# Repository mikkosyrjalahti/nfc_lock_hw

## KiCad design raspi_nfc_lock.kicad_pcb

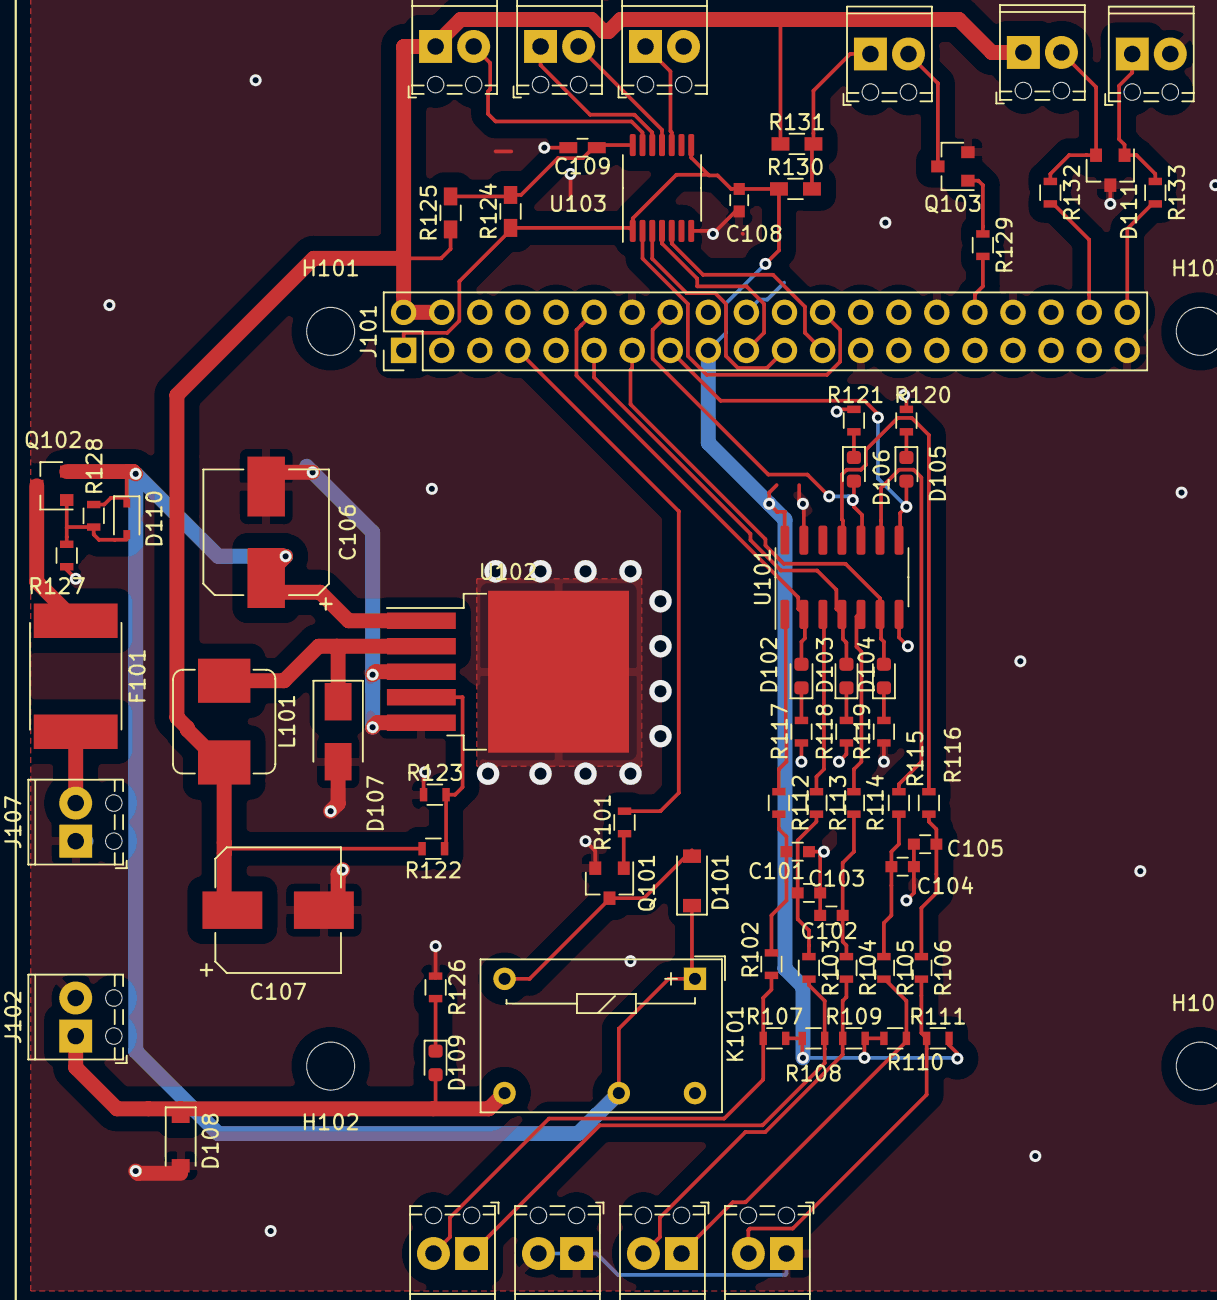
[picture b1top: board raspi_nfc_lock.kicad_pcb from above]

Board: 2 copper layers, 79 parts (0 on the bottom side), 56 nets.

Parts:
C101, C102, C103, C104, C105, C108: 100n; C_0603
C106: 220 μF 25V; CP_Elec_8x10
C107: 680μF 10V; CP_Elec_8x10.5
C109: 100n; C_0603_HandSoldering
D101, D108: SMF15A; D_SOD-123
D102, D103, D104, D105, D106: LED; D_0603_1608Metric
D107: SS34; D_SMA
D109: LED_OPEN; D_0603_1608Metric
D110: MM3Z12; D_SOD-323
D111: SP0502BAHT; SOT-23
F101: Polyfuse 1A; Fuse_SMD2920
H101, H102, H103, H104: MountingHole; MountingHole_3.2mm_M3
J101: Raspberry_Pi_2_3; Pin_Header_Straight_2x20_Pitch2.54mm
J102, J103, J104, J105, J106, J107, J108, J109, J110, J111, J112: Screw_Terminal_01x02; TerminalBlock_Phoenix_MPT-0,5-2-2.54_1x02_P2.54mm_Horizontal
J113: BUZZER; TerminalBlock_Phoenix_MPT-0,5-2-2.54_1x02_P2.54mm_Horizontal
K101: G6E; Relay_SPDT_Omron_G6E
L101: MWSA0603S-330MT; L_Bourns_SRP7028A_7.3x6.6mm
Q101, Q103: MMBT3904; SOT-23
Q102: Si2319CDS; SOT-23
R101, R129: 2k21; R_0603
R102, R103, R104, R105, R106: 10; R_0603
R107, R108, R109, R110, R111, R112, R113, R114, R115, R116, R117, R118, R119, R120, R121, R127: 4k7; R_0603
R122: 3k75; R_0603
R123: 1k21; R_0603
R124, R131: DNI; R_0603_HandSoldering
R125, R130: 0R; R_0603_HandSoldering
R126: 10k; R_0603
R128: 1M; R_0603
R132, R133: 470R; R_0603
U101: 74HC14; SOIC-14_3.9x8.7mm_P1.27mm
U102: LM2596S; TO-263-5_TabPin3
U103: TXB0104PW; TSSOP-14_4.4x5mm_P0.65mm

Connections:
+3V3: C108.1, J101.1, J101.17, R107.2, R108.2, R109.2, R110.2, R111.2, R124.1, R130.1, U101.14, U103.1, U103.8
+5V: C107.1, J101.2, J101.4, J108.1, J110.1, L101.2, R122.2, R125.1, R131.1
+12V: C106.1, D101.1, D110.1, K101.1, K101.10, Q102.2, R128.2, U102.1
/*CE0: J101.24, U103.2
/APA102_CLK: J101.40, R133.2
/APA102_DATA: J101.38, R132.2
/B1: D105.2, J101.15, U101.8
/B2: D106.2, J101.16, U101.10
/BUTTON_1: J105.1, R105.2, R110.1
/BUTTON_2: J106.2, R106.2, R111.1
/BUZZ: J113.2, Q103.3
/BUZZER: J101.32, R129.2
/DOOR: D102.2, J101.12, U101.2
/DOOR_SW: J103.2, R102.2, R107.1
/HANDLE: D104.2, J101.13, U101.6
/HANDLE_SW: J105.2, R104.2, R109.1
/LATCH: D103.2, J101.11, U101.4
/LATCH_SW: J103.1, R103.2, R108.1
/LED_CLK: D111.1, J109.1, R133.1
/LED_DATA: D111.2, J108.2, R132.1
/LOCK_SOLENOID: D108.1, D109.2, J102.1, K101.7
/MISO: J101.21, U103.3
/MOSI: J101.19, U103.4
/NFC_CS: J110.2, U103.13
/NFC_MISO: J111.1, U103.12
/NFC_MOSI: J111.2, U103.11
/NFC_SCK: J112.1, U103.10
/PWR_IN: F101.2, J107.2
/RELAY: J101.7, R101.2
/SCK: J101.23, U103.5
GND: C101.1, C102.1, C103.1, C104.1, C105.1, C106.2, C107.2, C108.2, C109.2, D107.2, D108.2, D111.3, J101.6, J101.9, J101.14, J101.20, J101.25, J101.30, J101.34, J101.39, J102.2, J104.1, J104.2, J106.1, J107.1, J109.2, J112.2, Q101.2, Q103.2, R117.1, R118.1, R119.1, R120.1, R121.1, R123.1, R126.1, R127.1, U101.7, U101.13, U102.3, U102.5, U103.7
unnamed: C101.2, R102.1, R112.2
unnamed: C102.2, R103.1, R113.2
unnamed: C103.2, R104.1, R114.2
unnamed: C104.2, R105.1, R115.2
unnamed: C105.2, R106.1, R116.2
unnamed: C109.1, R124.2, R125.2, U103.14
unnamed: D101.2, K101.6, Q101.3
unnamed: D102.1, R117.2
unnamed: D103.1, R118.2
unnamed: D104.1, R119.2
unnamed: D105.1, R120.2
unnamed: D106.1, R121.2
unnamed: D107.1, L101.1, U102.2
unnamed: D109.1, R126.2
unnamed: D110.2, Q102.1, R127.2, R128.1
unnamed: F101.1, Q102.3
unnamed: J113.1, R130.2, R131.2
unnamed: Q101.1, R101.1
unnamed: Q103.1, R129.1
unnamed: R112.1, U101.1
unnamed: R113.1, U101.3
unnamed: R114.1, U101.5
unnamed: R115.1, U101.9
unnamed: R116.1, U101.11
unnamed: R122.1, R123.2, U102.4

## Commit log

2020-05-01 Hacklab NFC lock shield for Raspi
2020-05-01 PCB for nfc lock
2020-05-01 Finished PCB design
2020-05-01 Cleanups
2020-05-02 Moved silkprints away from pads
2020-05-02 Removed thermals from regulator
2020-05-02 Changed TX0104 to TSSOP
2020-05-02 Changed some components to LCSC stock components Added LCSC references for BOM
